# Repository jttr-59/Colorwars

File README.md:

# Colorwars
this is a repository for the code used in my color wars board game project using TLC LED drivers based on the color wars game from "1234player games"

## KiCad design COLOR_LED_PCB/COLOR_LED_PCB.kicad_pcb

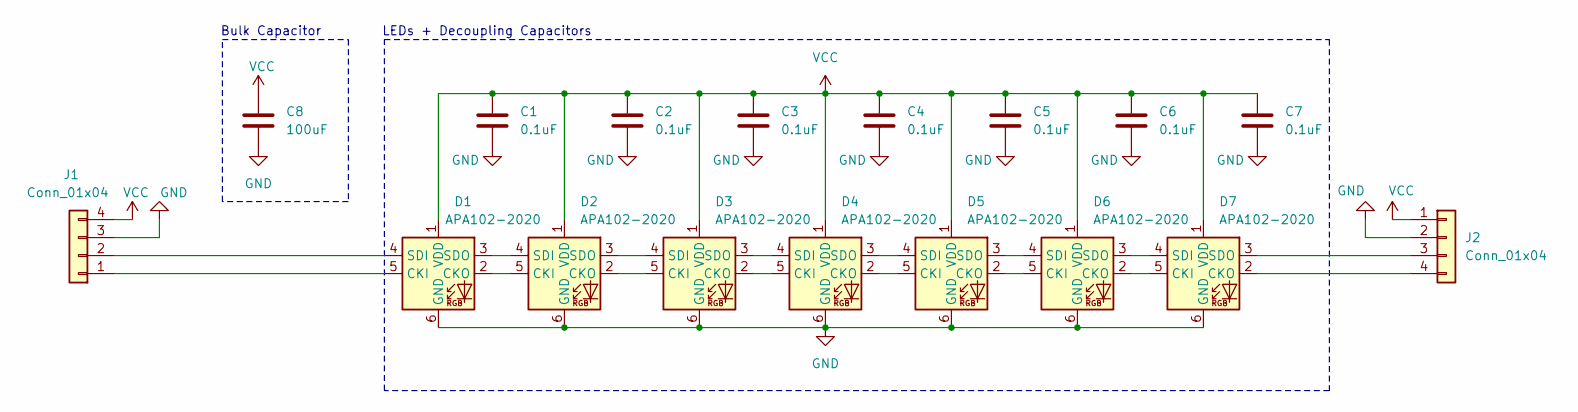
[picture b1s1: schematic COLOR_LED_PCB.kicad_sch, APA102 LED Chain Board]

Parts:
C1, C2, C3, C4, C5, C6, C7: 0.1uF; C_0805_2012Metric_Pad1.18x1.45mm_HandSolder
C8: 100uF; CP_Elec_6.3x5.8
D1, D2, D3, D4, D5, D6, D7: APA102-2020; LED-APA102-2020
J1, J2: Conn_01x04; PinHeader_1x04_P2.54mm_Vertical

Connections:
GND: C1.2, C2.2, C3.2, C4.2, C5.2, C6.2, C7.2, C8.2, D1.6 (GND), D2.6 (GND), D3.6 (GND), D4.6 (GND), D5.6 (GND), D6.6 (GND), D7.6 (GND), J1.3, J2.2
unnamed: D1.5 (CKI), J1.1
unnamed: D1.2 (CKO), D2.5 (CKI)
unnamed: D1.4 (SDI), J1.2
unnamed: D1.3 (SDO), D2.4 (SDI)
unnamed: D2.2 (CKO), D3.5 (CKI)
unnamed: D2.3 (SDO), D3.4 (SDI)
unnamed: D3.2 (CKO), D4.5 (CKI)
unnamed: D3.3 (SDO), D4.4 (SDI)
unnamed: D4.2 (CKO), D5.5 (CKI)
unnamed: D4.3 (SDO), D5.4 (SDI)
unnamed: D5.2 (CKO), D6.5 (CKI)
unnamed: D5.3 (SDO), D6.4 (SDI)
unnamed: D6.2 (CKO), D7.5 (CKI)
unnamed: D6.3 (SDO), D7.4 (SDI)
unnamed: D7.2 (CKO), J2.4
unnamed: D7.3 (SDO), J2.3
VCC: C1.1, C2.1, C3.1, C4.1, C5.1, C6.1, C7.1, C8.1, D1.1 (VDD), D2.1 (VDD), D3.1 (VDD), D4.1 (VDD), D5.1 (VDD), D6.1 (VDD), D7.1 (VDD), J1.4, J2.1

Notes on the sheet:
LEDs + Decoupling Capacitors
Bulk Capacitor

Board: 2 copper layers, 17 parts (0 on the bottom side), 18 nets, no tracks yet.

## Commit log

2026-01-26 Added Initial STM Code
2026-01-26 Finalized Project Code Implementation
2026-01-26 Updated system to fit with STM version 1.19
2026-04-27 Archived Old Info + New LED PCB Design
    took all the old firmware ald added it to an OLD file, new file added encluding a kicad file of the new PCB design
2026-05-07 Added Arduino Library And Code Test
2026-05-10 Finished Test Code Project
